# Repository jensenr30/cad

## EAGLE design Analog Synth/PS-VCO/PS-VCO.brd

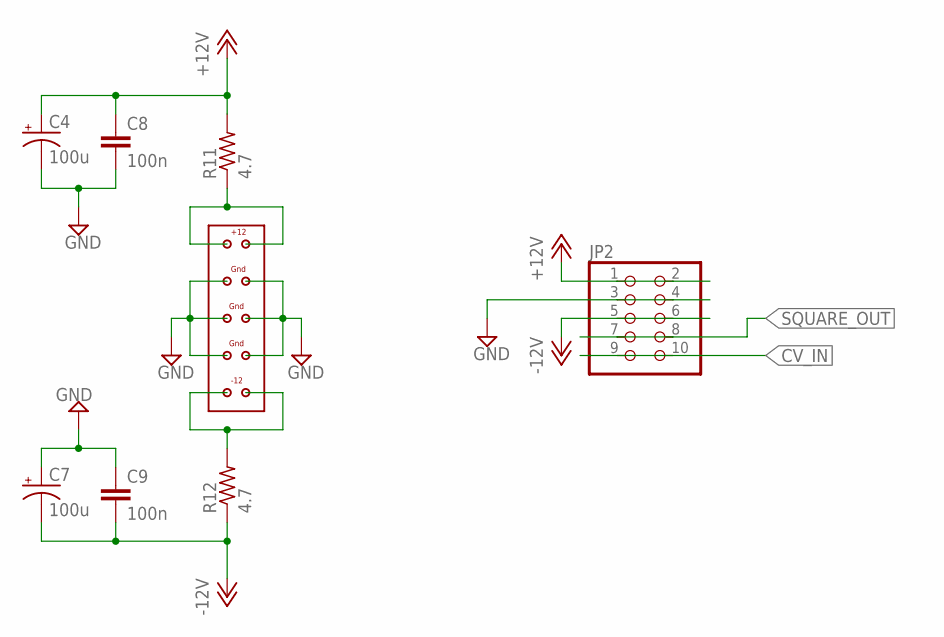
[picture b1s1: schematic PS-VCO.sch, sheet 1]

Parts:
C4, C7: 100u; E2,5-7
C8, C9: 100n; C0603
JP2: PINHD-2X5; 2X05
R11, R12: 4.7; R0603
U$3: EURORACK-POWER

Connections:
+12V: C4.+, C8.1, JP2.1, JP2.2, R11.2; also elsewhere on the board
-12V: C7.-, C9.2, JP2.5, JP2.6, R12.1; also elsewhere on the board
CV_IN: JP2.9, JP2.10; also elsewhere on the board
GND: C4.-, C7.+, C8.2, C9.1, JP2.3, JP2.4, U$3.P$3, U$3.P$4, U$3.P$5, U$3.P$6, U$3.P$7, U$3.P$8; also elsewhere on the board
unnamed: R12.2, U$3.P$9, U$3.P$10
unnamed: R11.1, U$3.P$1, U$3.P$2
SQUARE_OUT: JP2.7, JP2.8; also elsewhere on the board

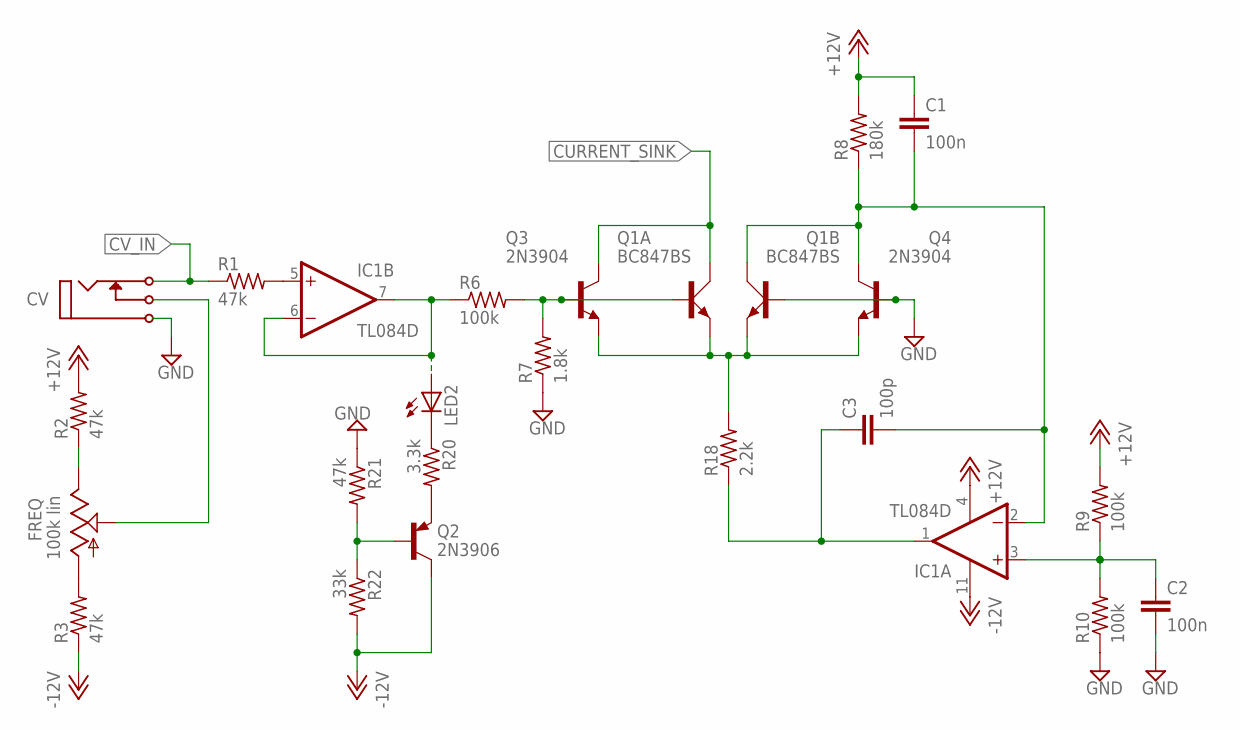
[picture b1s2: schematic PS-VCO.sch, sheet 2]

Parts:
C1, C2: 100n; C0603
C3: 100p; C0603
CV: CV; MONO_JACK
FREQ: 100k lin; B64Y
IC1: TL084D; SO14
LED2: LED_ELD260; LED_LD260
Q1: BC847BS; SOT363_PHILIPS
Q2: 2N3906; TO92
Q3, Q4: 2N3904; TO92
R1, R2, R3, R21: 47k; R0603
R6, R9, R10: 100k; R0603
R7: 1.8k; R0603
R8: 180k; R0603
R18: 2.2k; R0603
R20: 3.3k; R0603
R22: 33k; R0603

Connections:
+12V: C1.1, IC1.4 (V+), R2.2, R8.2, R9.2; also elsewhere on the board
-12V: IC1.11 (V-), Q2.1 (C), R3.1, R22.2; also elsewhere on the board
CURRENT_SINK: Q1.6 (C), Q3.1 (C); also elsewhere on the board
CV_IN: CV.P$2 (P2), R1.1; also elsewhere on the board
CV_LED: IC1.6 (-IN), IC1.7 (OUT), LED2.A, R6.1
GND: C2.2, CV.P$1, Q1.5 (B), Q4.2 (B), R7.1, R10.1, R21.1; also elsewhere on the board
unnamed: Q1.1 (E), Q1.4 (E), Q3.3 (E), Q4.3 (E), R18.2
unnamed: Q1.2 (B), Q3.2 (B), R6.2, R7.2
unnamed: C2.1, IC1.3 (+IN), R9.1, R10.2
unnamed: FREQ.E, R2.1
unnamed: FREQ.A, R3.2
unnamed: CV.P$3 (P3), FREQ.S
unnamed: IC1.5 (+IN), R1.2
unnamed: Q2.3 (E), R20.2
unnamed: LED2.K (C), R20.1
unnamed: Q2.2 (B), R21.2, R22.1
unnamed: C3.1, IC1.1 (OUT), R18.1
unnamed: C1.2, C3.2, IC1.2 (-IN), Q1.3 (C), Q4.1 (C), R8.1

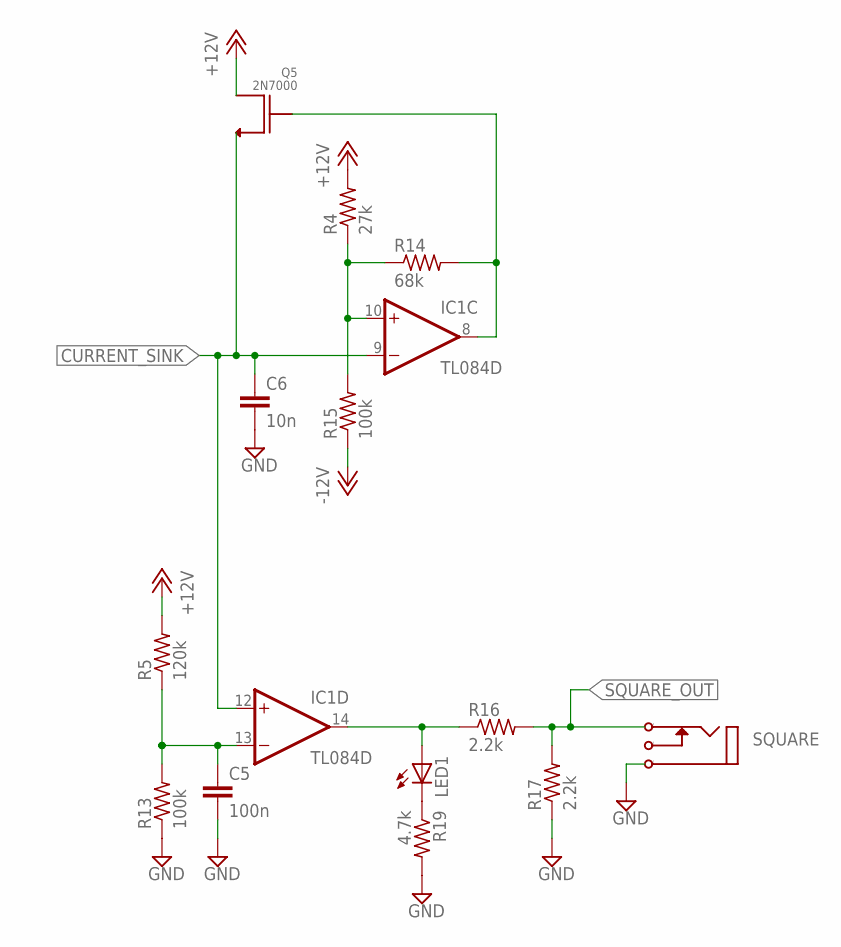
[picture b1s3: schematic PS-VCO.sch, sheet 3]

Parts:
C5: 100n; C0603
C6: 10n; C0603
IC1: TL084D; SO14
LED1: LED_ELD260; LED_LD260
Q5: 2N7000
R4: 27k; R0603
R5: 120k; R0603
R13, R15: 100k; R0603
R14: 68k; R0603
R16, R17: 2.2k; R0603
R19: 4.7k; R0603
SQUARE: I/O; MONO_JACK

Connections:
+12V: Q5.D, R4.2, R5.2; also elsewhere on the board
-12V: R15.1; also elsewhere on the board
CURRENT_SINK: C6.1, IC1.9 (-IN), IC1.12 (+IN), Q5.S; also elsewhere on the board
GND: C5.2, C6.2, R13.1, R17.1, R19.2, SQUARE.P$1; also elsewhere on the board
unnamed: IC1.10 (+IN), R4.1, R14.1, R15.2
unnamed: LED1.K (C), R19.1
unnamed: C5.1, IC1.13 (-IN), R5.1, R13.2
unnamed: IC1.14 (OUT), LED1.A, R16.1
unnamed: IC1.8 (OUT), Q5.G, R14.2
SQUARE_OUT: R16.2, R17.2, SQUARE.P$2 (P2); also elsewhere on the board

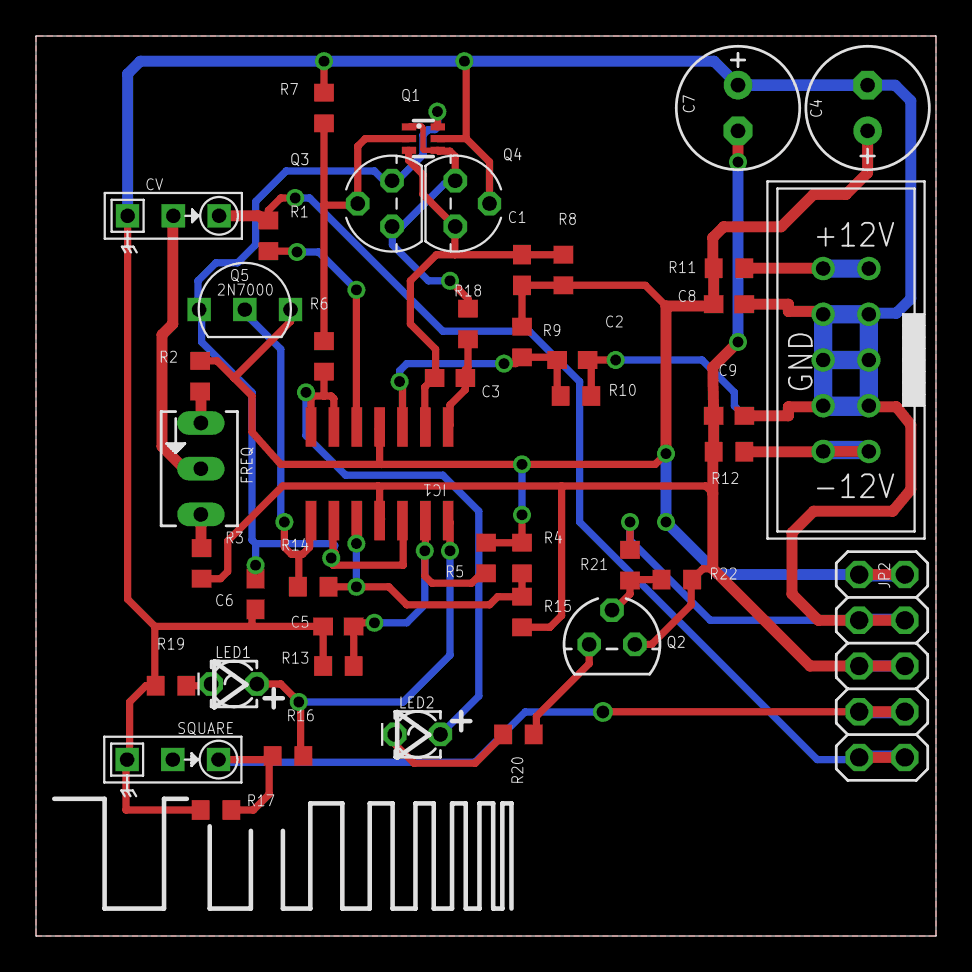
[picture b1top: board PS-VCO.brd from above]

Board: 2 copper layers, 50.0 x 50.0 mm, 44 parts (0 on the bottom side), 26 nets.

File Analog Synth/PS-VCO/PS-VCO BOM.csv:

Qty,Value,Device,Package,Parts,Description
1,EURORACK-POWER,EURORACK-POWER,EURORACK-POWER,U$3,
1,I/O,MONO_JACK,MONO_JACK,SQUARE,
1,180k,R-US_R0603,R0603,R8,"RESISTOR, American symbol"
1,1.8k,R-US_R0603,R0603,R7,"RESISTOR, American symbol"
5,100k,R-US_R0603,R0603,"R6, R9, R10, R13, R15","RESISTOR, American symbol"
1,120k,R-US_R0603,R0603,R5,"RESISTOR, American symbol"
1,27k,R-US_R0603,R0603,R4,"RESISTOR, American symbol"
1,33k,R-US_R0603,R0603,R22,"RESISTOR, American symbol"
1,3.3k,R-US_R0603,R0603,R20,"RESISTOR, American symbol"
1,4.7k,R-US_R0603,R0603,R19,"RESISTOR, American symbol"
3,2.2k,R-US_R0603,R0603,"R16, R17, R18","RESISTOR, American symbol"
1,68k,R-US_R0603,R0603,R14,"RESISTOR, American symbol"
2,4.7,R-US_R0603,R0603,"R11, R12","RESISTOR, American symbol"
4,47k,R-US_R0603,R0603,"R1, R2, R3, R21","RESISTOR, American symbol"
1,2N7000,2N7000,2N7000,Q5,
2,2N3904,2N3904,TO92,"Q3, Q4",NPN TRANSISTOR
1,2N3906,2N3906,TO92,Q2,PNP Transistor
1,BC847BS,BC847BS,SOT363_PHILIPS,Q1,NPN general purpose double transistor
2,,LED_ELD260,LED_LD260,"LED1, LED2",LED
1,,PINHD-2X5,2X05,JP2,PIN HEADER
1,TL084D,TL084D,SO14,IC1,OP AMP
1,100k lin,TRIM_US-B64Y,B64Y,FREQ,POTENTIOMETER
1,CV,MONO_JACK,MONO_JACK,CV,
1,10n,C-EUC0603,C0603,C6,"CAPACITOR, European symbol"
2,100u,CPOL-USE2.5-7,"E2,5-7","C4, C7","POLARIZED CAPACITOR, American symbol"
1,100p,C-EUC0603,C0603,C3,"CAPACITOR, European symbol"
5,100n,C-EUC0603,C0603,"C1, C2, C5, C8, C9","CAPACITOR, European symbol"
